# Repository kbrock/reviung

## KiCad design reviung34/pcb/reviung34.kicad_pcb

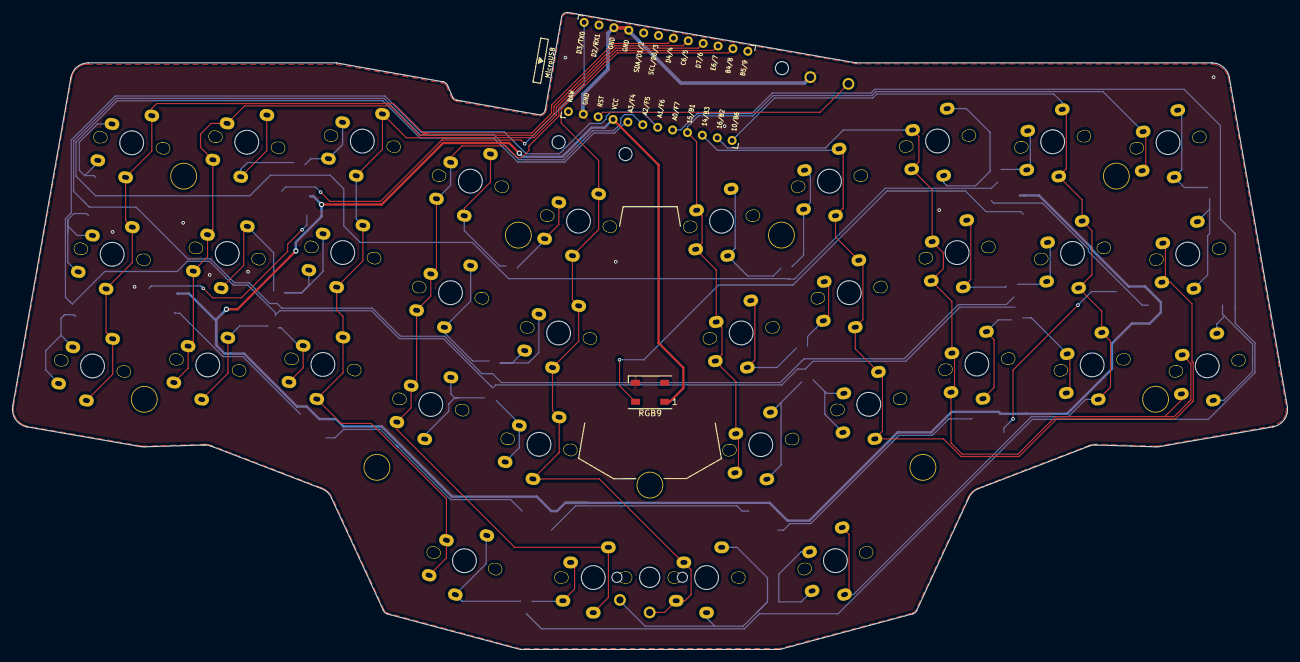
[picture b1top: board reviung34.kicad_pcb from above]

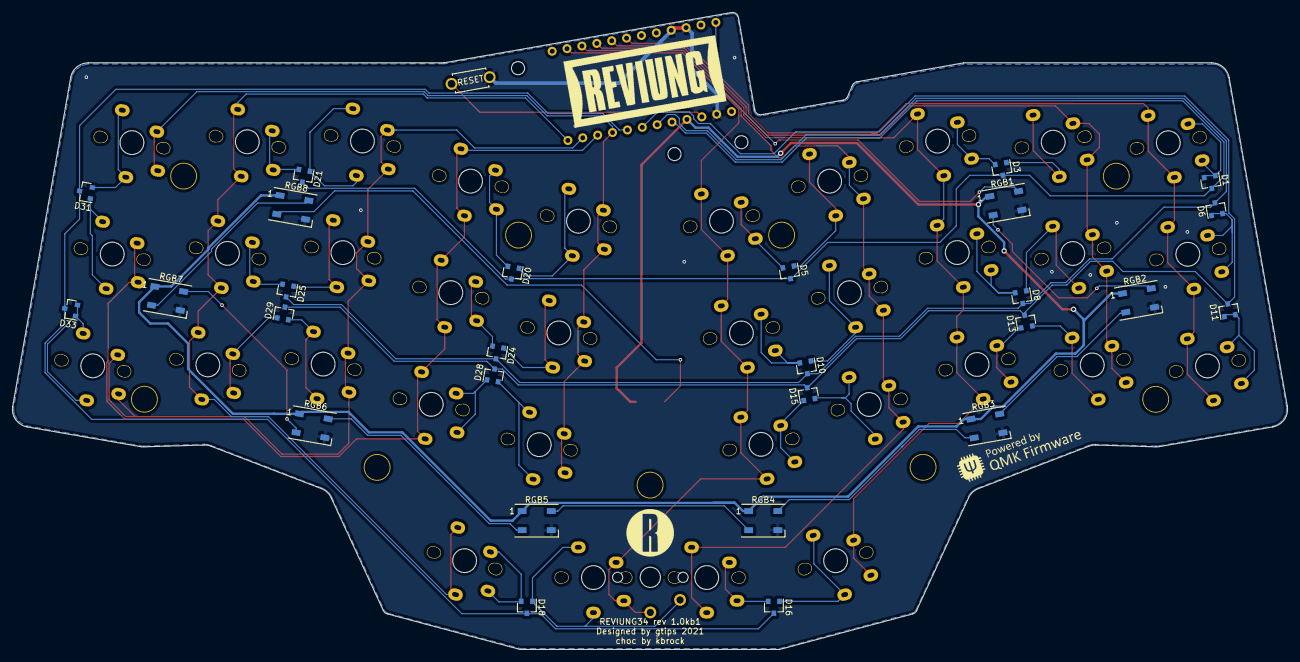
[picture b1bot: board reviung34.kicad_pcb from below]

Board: 2 copper layers, 214.3 x 107.1 mm, 77 parts (28 on the bottom side), 59 nets.

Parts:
D1, D3, D5, D6, D8, D10, D11, D13, D15, D16, D18, D20, D21, D24, D25, D28, D29, D31, D33: BAV70; SOT-23
H1, H2, H3, H4, H5, H6, H7, H8, H9: HOLE_4.2mm
RESET1: SW_PUSH; ResetSW_1side
RGB1, RGB2, RGB3, RGB4, RGB5, RGB6, RGB7, RGB8, RGB9: WS2812B; LED_WS2812B_PLCC4_5.0x5.0mm_P3.2mm
Ref**: Val**; HOLE_2.2mm
Ref**#2, Ref**#3: Val**; HOLE_2.2mm
SW1, SW2, SW3, SW4, SW5, SW6, SW7, SW8, SW9, SW10, SW11, SW12, SW13, SW14, SW15, SW16, SW17, SW18, SW19, SW20, SW21, SW22, SW23, SW24, SW25, SW26, SW27, SW28, SW29, SW30, SW31, SW32, SW33, SW34: SW_PUSH; CherryMX_Choc_1u
SW35: SW_PUSH; Kailh-PG1350-1u-NoLED
U1: ProMicro; ProMicro_v3

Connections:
GND: RESET1.2, RGB1.3, RGB2.3, RGB3.3, RGB4.3, RGB5.3, RGB6.3, RGB7.3, RGB8.3, RGB9.3, U1.3, U1.4, U1.23
LED: RGB1.4, U1.1
unnamed: D1.1, D1.2, SW1.1
unnamed: D3.1, SW2.2
unnamed: D3.2, SW3.1
unnamed: D5.1, SW4.2
unnamed: D5.2, SW5.1
unnamed: D6.1, D6.2, SW6.1
unnamed: D8.1, SW7.2
unnamed: D8.2, SW8.1
unnamed: D10.1, SW9.2
unnamed: D10.2, SW10.1
unnamed: D11.1, D11.2, SW11.1
unnamed: D13.1, SW13.1
unnamed: D13.2, SW12.2
unnamed: D15.1, SW15.1
unnamed: D15.2, SW14.2
unnamed: D16.1, SW16.2
unnamed: D16.2, SW17.1
unnamed: D18.1, SW18.2, SW35.2
unnamed: D18.2, SW34.1
unnamed: D20.1, SW19.2
unnamed: D20.2, SW20.1
unnamed: D21.1, SW21.2
unnamed: D21.2, SW22.1
unnamed: D24.1, SW23.2
unnamed: D24.2, SW24.1
unnamed: D25.1, SW25.2
unnamed: D25.2, SW26.1
unnamed: D28.1, SW28.1
unnamed: D28.2, SW27.2
unnamed: D29.1, SW30.1
unnamed: D29.2, SW29.2
unnamed: D31.1, SW32.2
unnamed: D31.2, SW31.2
unnamed: D33.1, D33.2, SW33.2
unnamed: RGB1.2, RGB2.4
unnamed: RGB2.2, RGB3.4
unnamed: RGB3.2, RGB4.4
unnamed: RGB4.2, RGB5.4
unnamed: RGB5.2, RGB6.4
unnamed: RGB6.2, RGB7.4
unnamed: RGB7.2, RGB8.4
unnamed: RGB8.2, RGB9.4
VCC: RGB1.1, RGB2.1, RGB3.1, RGB4.1, RGB5.1, RGB6.1, RGB7.1, RGB8.1, RGB9.1, U1.21
col0: SW1.2, SW6.2, SW11.2, U1.7
col1: SW2.1, SW7.1, SW12.1, U1.8
col2: SW3.2, SW8.2, SW13.2, SW16.1, U1.9
col3: SW4.1, SW9.1, SW14.1, SW17.2, U1.10
col4: SW5.2, SW10.2, SW15.2, SW18.1, SW35.1, U1.11
col5: SW19.1, SW23.1, SW27.1, SW31.1, U1.16
col6: SW20.2, SW24.2, SW28.2, SW32.1, U1.15
col7: SW21.1, SW25.1, SW29.1, SW33.1, U1.14
col8: SW22.2, SW26.2, SW30.2, SW34.2, U1.13
reset: RESET1.1, U1.22
row0: D1.3, D3.3, D5.3, D20.3, D21.3, U1.20
row1: D6.3, D8.3, D10.3, D24.3, D25.3, U1.19
row2: D11.3, D13.3, D15.3, D28.3, D29.3, U1.18
row3: D16.3, D18.3, D31.3, D33.3, U1.17

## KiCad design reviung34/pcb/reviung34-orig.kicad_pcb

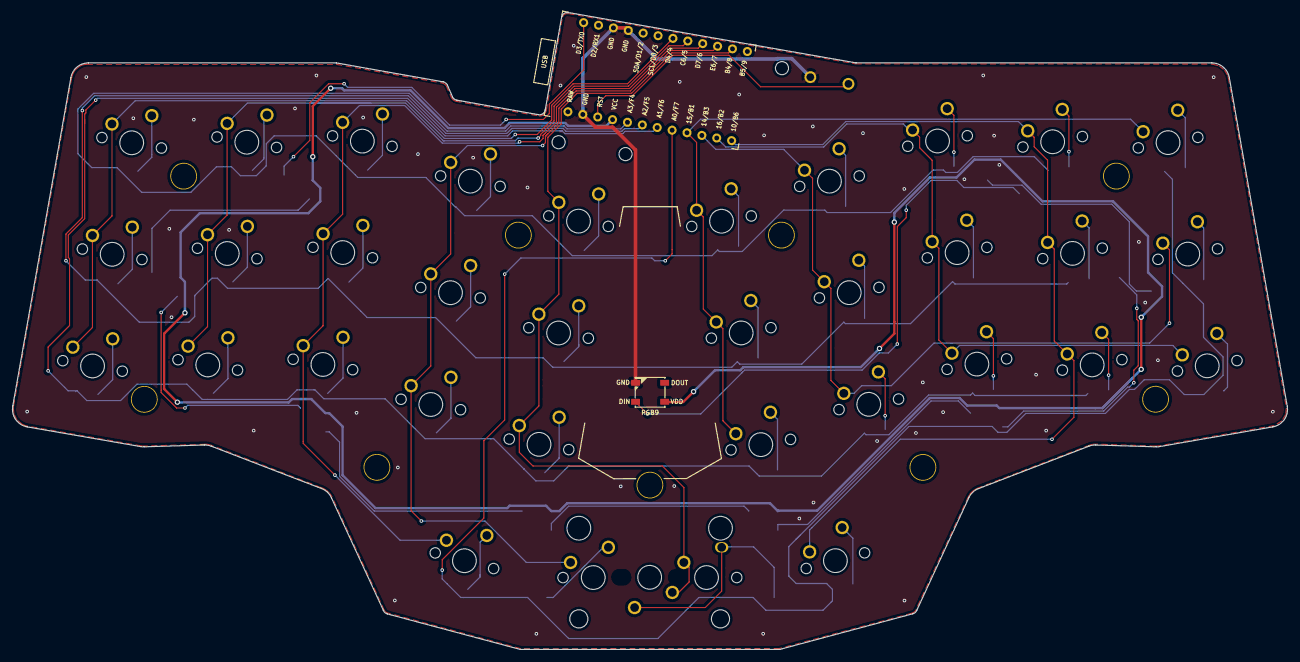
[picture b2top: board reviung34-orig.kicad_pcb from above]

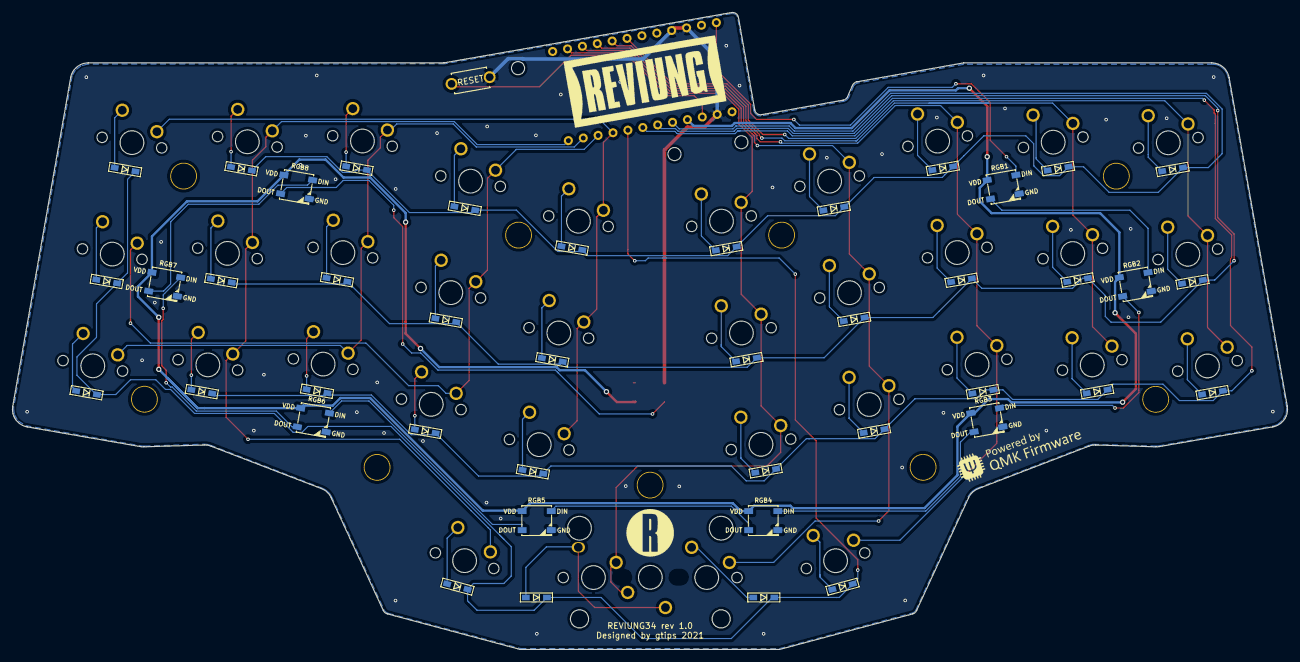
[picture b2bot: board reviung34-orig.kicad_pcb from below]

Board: 2 copper layers, 214.3 x 107.1 mm, 92 parts (43 on the bottom side), 59 nets.

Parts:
D1, D2, D3, D4, D5, D6, D7, D8, D9, D10, D11, D12, D13, D14, D15, D16, D17, D18, D19, D20, D21, D22, D23, D24, D25, D26, D27, D28, D29, D30, D31, D32, D33, D34: 1N4148W; D3_SMD_1side
H1, H2, H3, H4, H5, H6, H7, H8, H9: HOLE_4.2mm
RESET1: SW_PUSH; ResetSW_1side
RGB1, RGB2, RGB3, RGB4, RGB5, RGB6, RGB7, RGB8, RGB9: WS2812B; LED_WS2812B_PLCC4_5.0x5.0mm_P3.2mm
Ref**: Val**; HOLE_2.2mm
Ref**#2, Ref**#3: Val**; HOLE_2.2mm
SW1, SW2, SW3, SW4, SW5, SW6, SW7, SW8, SW9, SW10, SW11, SW12, SW13, SW14, SW15, SW16, SW19, SW20, SW21, SW22, SW23, SW24, SW25, SW26, SW27, SW28, SW29, SW30, SW31, SW32, SW33, SW34: SW_PUSH; MXOnly-1U-NoLED
SW17: SW_PUSH; MXOnly-1U-5pinRcut
SW18: SW_PUSH; MXOnly-1U-5pinLcut
SW35: SW_PUSH; MXOnly-2U-NoLED-or1Ux2
U1: ProMicro

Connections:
GND: RESET1.2, RGB1.3, RGB2.3, RGB3.3, RGB4.3, RGB5.3, RGB6.3, RGB7.3, RGB8.3, RGB9.3, U1.3, U1.4, U1.23
LED: RGB1.4, U1.1
unnamed: D1.2, SW1.2
unnamed: D2.2, SW2.2
unnamed: D3.2, SW3.2
unnamed: D4.2, SW4.2
unnamed: D5.2, SW5.2
unnamed: D6.2, SW6.2
unnamed: D7.2, SW7.2
unnamed: D8.2, SW8.2
unnamed: D9.2, SW9.2
unnamed: D10.2, SW10.2
unnamed: D11.2, SW11.2
unnamed: D12.2, SW12.2
unnamed: D13.2, SW13.2
unnamed: D14.2, SW14.2
unnamed: D15.2, SW15.2
unnamed: D16.2, SW16.2
unnamed: D17.2, SW17.2
unnamed: D18.2, SW18.2, SW35.2
unnamed: D19.2, SW19.2
unnamed: D20.2, SW20.2
unnamed: D21.2, SW21.2
unnamed: D22.2, SW22.2
unnamed: D23.2, SW23.2
unnamed: D24.2, SW24.2
unnamed: D25.2, SW25.2
unnamed: D26.2, SW26.2
unnamed: D27.2, SW27.2
unnamed: D28.2, SW28.2
unnamed: D29.2, SW29.2
unnamed: D30.2, SW30.2
unnamed: D31.2, SW31.2
unnamed: D32.2, SW32.2
unnamed: D33.2, SW33.2
unnamed: D34.2, SW34.2
unnamed: RGB1.2, RGB2.4
unnamed: RGB2.2, RGB3.4
unnamed: RGB3.2, RGB4.4
unnamed: RGB4.2, RGB5.4
unnamed: RGB5.2, RGB6.4
unnamed: RGB6.2, RGB7.4
unnamed: RGB7.2, RGB8.4
unnamed: RGB8.2, RGB9.4
VCC: RGB1.1, RGB2.1, RGB3.1, RGB4.1, RGB5.1, RGB6.1, RGB7.1, RGB8.1, RGB9.1, U1.21
col0: SW1.1, SW6.1, SW11.1, U1.7
col1: SW2.1, SW7.1, SW12.1, U1.8
col2: SW3.1, SW8.1, SW13.1, SW16.1, U1.9
col3: SW4.1, SW9.1, SW14.1, SW17.1, U1.10
col4: SW5.1, SW10.1, SW15.1, SW18.1, SW35.1, U1.11
col5: SW19.1, SW23.1, SW27.1, SW31.1, U1.16
col6: SW20.1, SW24.1, SW28.1, SW32.1, U1.15
col7: SW21.1, SW25.1, SW29.1, SW33.1, U1.14
col8: SW22.1, SW26.1, SW30.1, SW34.1, U1.13
reset: RESET1.1, U1.22
row0: D1.1, D2.1, D3.1, D4.1, D5.1, D19.1, D20.1, D21.1, D22.1, U1.20
row1: D6.1, D7.1, D8.1, D9.1, D10.1, D23.1, D24.1, D25.1, D26.1, U1.19
row2: D11.1, D12.1, D13.1, D14.1, D15.1, D27.1, D28.1, D29.1, D30.1, U1.18
row3: D16.1, D17.1, D18.1, D31.1, D32.1, D33.1, D34.1, U1.17

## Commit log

2021-11-20 using kbd switches and pro-micro
2021-11-21 keyboard submodules from kbd and keebio
2021-11-21 choc version of r34
